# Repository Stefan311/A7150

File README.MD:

# A7150 (CM1910)
### What is the A7150?
It's an old computer from the east german "Robotron" company. See [Wikipedia](https://de.wikipedia.org/wiki/A_7150)
### Why is the rest of this project in german language?
It's made for and with an german audience in mind. The A7150 is rare outside the former east german country anyway.
### Projekte
[IDE-Kontroller AFI-K5173](AFI-K5173/)
[Experimentier-Karte](Exp/)

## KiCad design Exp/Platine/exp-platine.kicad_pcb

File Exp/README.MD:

# Experimentier-Karte für A71x0
## Layout in KiCad
[Revision 1](Platine/)
## Projekte / Beispiele
### JTAG-Flasher
Ein Projekt für den ESP32, das kann benutzt werden, um über WLAN den CPLD zu konfigurieren.
[Flasher](Projekte/esp32_jtag_CPLD_flasher/)
### Einfacher I/O Port
Ein Beispiel für einen einfachen I/O-Port.
[IO-Port](Projekte/simple_io_port/)
### Drucker-Port
Ein zusätzlicher Drucker-Port, kann zum Drucken, oder für Fern-Verbindungen mit dem Norton-Kommander oder Laplink benutzt werden.
[Druckerport](Projekte/printer_port/)
## Tools
### Flasher
Kleine Scripte um Xilinx iMPACT und flashen mit dem ESP32 zu automatisieren.
(Projekte/tools/flash/)
## Beschreibungen / Wissen
...kommt noch...

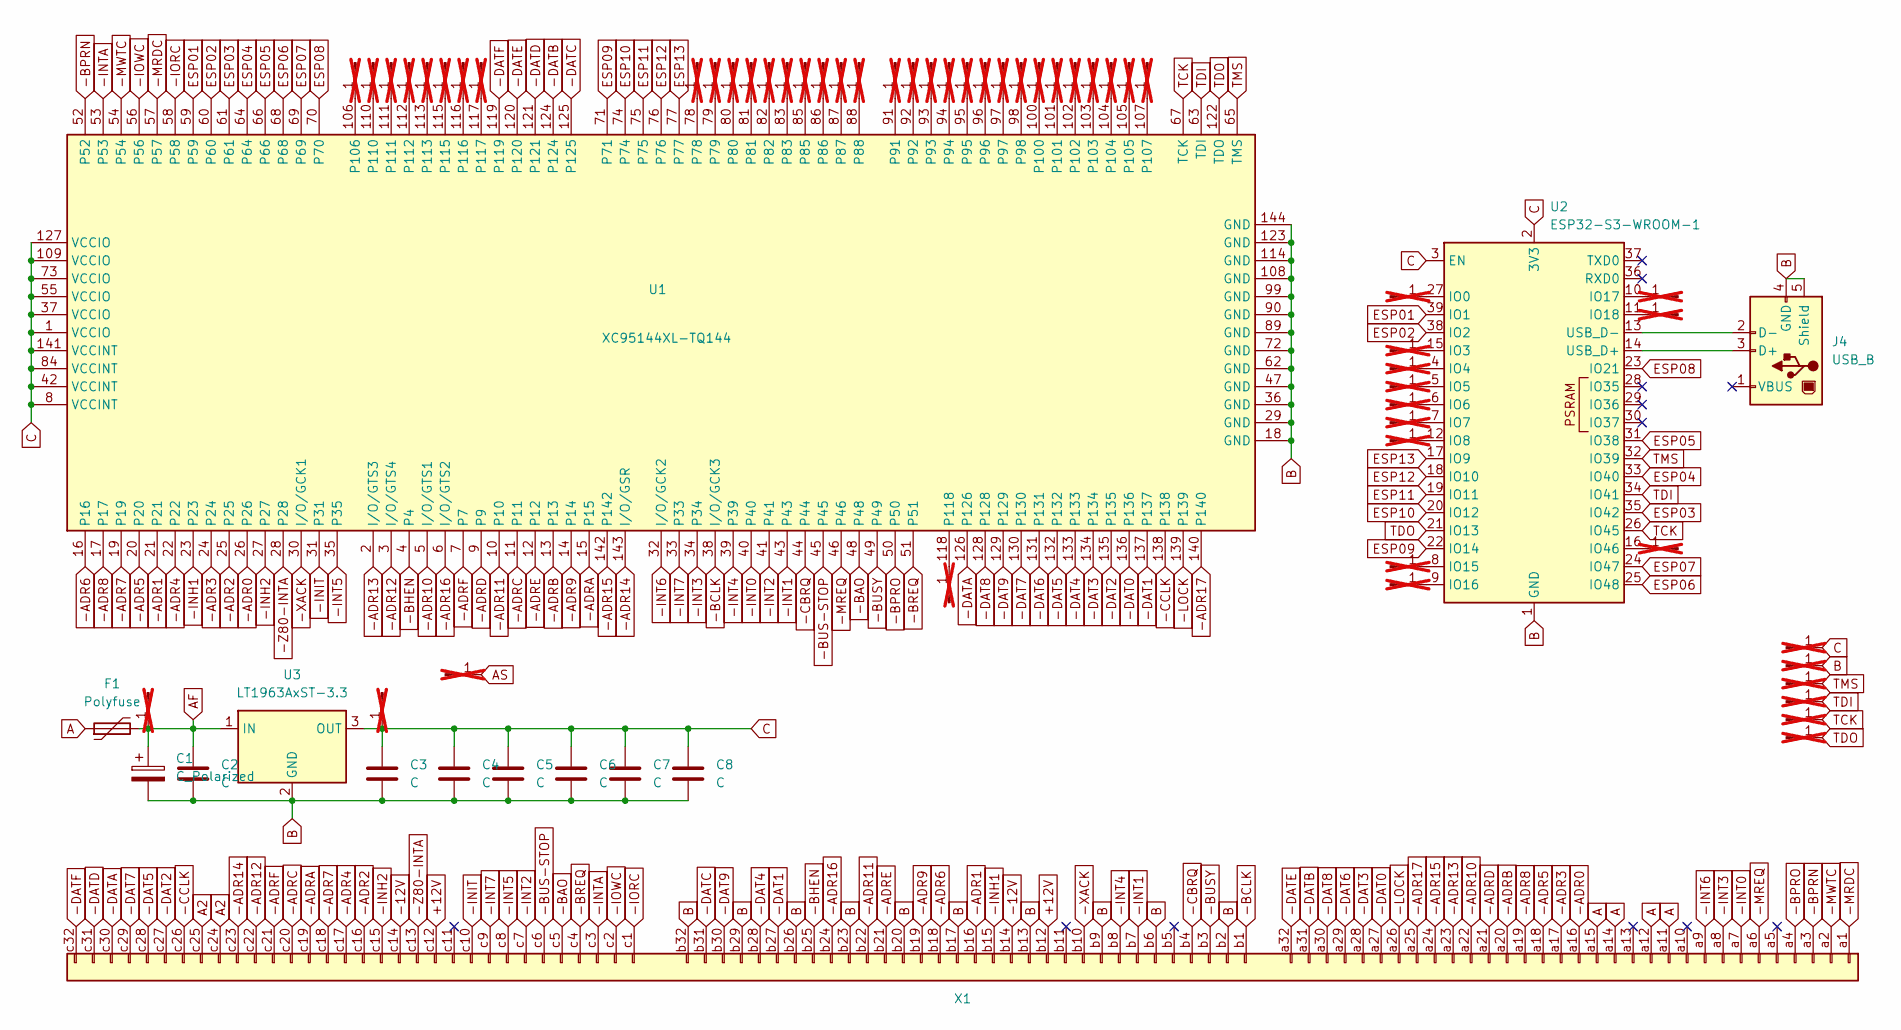
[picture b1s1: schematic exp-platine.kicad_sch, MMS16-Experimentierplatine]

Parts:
C1: C_Polarized; C_Radial_D6.3mm_H5.0mm_P2.50mm
C2, C3, C4, C5, C6, C7, C8: C; C_0805_2012Metric_Pad1.18x1.45mm_HandSolder
F1: Polyfuse; Fuse_Bourns_MF-RG300
J1, J2, J3, J5, J6, J7, J8, J9, J10, J11, J12, J13, J14, J15, J16, J17, J18, J19, J20, J21, J22, J23, J24, J25, J26, J27, J28, J29, J30, J31, J32, J33, J34, J35, J36, J37, J38, J39, J40, J41, J42, J43, J44, J45, J46, J47, J48, J49, J50, J51, J52, J53, J54, J55, J56: Conn_01x01_Pin; PinHeader_1x01_P2.54mm_Vertical; not fitted
J4: USB_B; USB_B_Lumberg_2411_02_Horizontal
U1: XC95144XL-TQ144; TQFP-144_20x20mm_P0.5mm
U2: ESP32-S3-WROOM-1
U3: LT1963AxST-3.3; SOT-223-3_TabPin2
X1: DIN41612_03x32_ABC; DIN41612_C_3x32_Male_Horizontal_THT

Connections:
+12V: X1.b12, X1.c12
-12V: X1.b14, X1.c14
-ADR0: U1.26, X1.a16
-ADR1: U1.21, X1.b16
-ADR2: U1.25, X1.c16
-ADR3: U1.24, X1.a17
-ADR4: U1.22, X1.c17
-ADR5: U1.20, X1.a18
-ADR6: U1.16, X1.b18
-ADR7: U1.19, X1.c18
-ADR8: U1.17, X1.a19
-ADR9: U1.14, X1.b19
-ADR10: U1.5 (I/O/GTS1), X1.a22
-ADR11: U1.10, X1.b22
-ADR12: U1.3 (I/O/GTS4), X1.c22
-ADR13: U1.2 (I/O/GTS3), X1.a23
-ADR14: U1.143 (I/O/GSR), X1.c23
-ADR15: U1.142, X1.a24
-ADR16: U1.6 (I/O/GTS2), X1.b24
-ADR17: U1.140, X1.a25
-ADRA: U1.15, X1.c19
-ADRB: U1.13, X1.a20
-ADRC: U1.11, X1.c20
-ADRD: U1.9, X1.a21
-ADRE: U1.12, X1.b21
-ADRF: U1.7, X1.c21
-BAO: U1.48, X1.c5
-BCLK: U1.38 (I/O/GCK3), X1.b1
-BHEN: U1.4, X1.b25
-BPRN: U1.52, X1.a3
-BPRO: U1.50, X1.a4
-BREQ: U1.51, X1.c4
-BUS-STOP: U1.45, X1.c6
-BUSY: U1.49, X1.b3
-CBRQ: U1.44, X1.b4
-CCLK: U1.138, X1.c26
-DAT0: U1.136, X1.a27
-DAT1: U1.137, X1.b27
-DAT2: U1.135, X1.c27
-DAT3: U1.134, X1.a28
-DAT4: U1.133, X1.b28
-DAT5: U1.132, X1.c28
-DAT6: U1.131, X1.a29
-DAT7: U1.130, X1.c29
-DAT8: U1.128, X1.a30
-DAT9: U1.129, X1.b30
-DATA: U1.126, X1.c30
-DATB: U1.124, X1.a31
-DATC: U1.125, X1.b31
-DATD: U1.121, X1.c31
-DATE: U1.120, X1.a32
-DATF: U1.119, X1.c32
-INH1: U1.23, X1.b15
-INH2: U1.27, X1.c15
-INIT: U1.31, X1.c10
-INT0: U1.40, X1.a7
-INT1: U1.43, X1.b7
-INT2: U1.41, X1.c7
-INT3: U1.34, X1.a8
-INT4: U1.39, X1.b8
-INT5: U1.35, X1.c8
-INT6: U1.32 (I/O/GCK2), X1.a9
-INT7: U1.33, X1.c9
-INTA: U1.53, X1.c3
-IORC: U1.58, X1.c1
-IOWC: U1.56, X1.c2
-LOCK: U1.139, X1.a26
-MRDC: U1.57, X1.a1
-MREQ: U1.46, X1.a6
-MWTC: U1.54, X1.a2
-XACK: U1.30 (I/O/GCK1), X1.b10
-Z80-INTA: U1.28, X1.c13
A: F1.1, X1.a11, X1.a12, X1.a14, X1.a15
A2: X1.c24, X1.c25
AF: C1.1, C2.1, F1.2, J34.1, U3.1 (IN)
AS: J54.1
B: C1.2, C2.2, C3.2, C4.2, C5.2, C6.2, C7.2, C8.2, J4.4 (GND), J4.5 (Shield), J36.1, U1.18 (GND), U1.29 (GND), U1.36 (GND), U1.47 (GND), U1.62 (GND), U1.72 (GND), U1.89 (GND), U1.90 (GND), U1.99 (GND), U1.108 (GND), U1.114 (GND), U1.123 (GND), U1.144 (GND), U2.1 (GND), U2.40 (GND), U2.41 (GND), U3.2 (GND), X1.b2, X1.b6, X1.b9, X1.b13, X1.b17, X1.b20, X1.b23, X1.b26, X1.b29, X1.b32
C: C3.1, C4.1, C5.1, C6.1, C7.1, C8.1, J37.1, J53.1, U1.1 (VCCIO), U1.8 (VCCINT), U1.37 (VCCIO), U1.42 (VCCINT), U1.55 (VCCIO), U1.73 (VCCIO), U1.84 (VCCINT), U1.109 (VCCIO), U1.127 (VCCIO), U1.141 (VCCINT), U2.2 (3V3), U2.3 (EN), U3.3 (OUT)
ESP01: U1.59, U2.39 (IO1)
ESP02: U1.60, U2.38 (IO2)
ESP03: U1.61, U2.35 (IO42)
ESP04: U1.64, U2.33 (IO40)
ESP05: U1.66, U2.31 (IO38)
ESP06: U1.68, U2.25 (IO48)
ESP07: U1.69, U2.24 (IO47)
ESP08: U1.70, U2.23 (IO21)
ESP09: U1.71, U2.22 (IO14)
ESP10: U1.74, U2.20 (IO12)
ESP11: U1.75, U2.19 (IO11)
ESP12: U1.76, U2.18 (IO10)
ESP13: U1.77, U2.17 (IO9)
unnamed: J1.1, U1.118
unnamed: J2.1, U1.117
unnamed: J3.1, U1.116
unnamed: J4.3 (D+), U2.14 (USB_D+)
unnamed: J4.2 (D-), U2.13 (USB_D-)
unnamed: J5.1, U1.115
unnamed: J6.1, U1.113
unnamed: J7.1, U1.112
unnamed: J8.1, U1.111
unnamed: J9.1, U1.110
unnamed: J10.1, U1.107
unnamed: J11.1, U1.106
unnamed: J12.1, U1.105
unnamed: J13.1, U1.103
unnamed: J14.1, U1.104
unnamed: J15.1, U1.98
unnamed: J16.1, U1.100
unnamed: J17.1, U1.101
unnamed: J18.1, U1.102
unnamed: J19.1, U1.80
unnamed: J20.1, U1.91
unnamed: J21.1, U1.92
unnamed: J22.1, U1.93
unnamed: J23.1, U1.94
unnamed: J24.1, U1.95
unnamed: J25.1, U1.96
unnamed: J26.1, U1.97
unnamed: J27.1, U1.81
unnamed: J28.1, U1.82
unnamed: J29.1, U1.83
unnamed: J30.1, U1.85
unnamed: J31.1, U1.86
unnamed: J32.1, U1.87
unnamed: J33.1, U1.88
unnamed: J35.1, U2.4 (IO4)
unnamed: J40.1, U1.78
unnamed: J41.1, U1.79
unnamed: J42.1, U2.5 (IO5)
unnamed: J43.1, U2.6 (IO6)
unnamed: J44.1, U2.7 (IO7)
unnamed: J45.1, U2.8 (IO15)
unnamed: J46.1, U2.9 (IO16)
unnamed: J47.1, U2.10 (IO17)
unnamed: J48.1, U2.11 (IO18)
unnamed: J49.1, U2.12 (IO8)
unnamed: J51.1, U2.15 (IO3)
unnamed: J52.1, U2.16 (IO46)
unnamed: J55.1, U2.27 (IO0)
TCK: J50.1, U1.67 (TCK), U2.26 (IO45)
TDI: J39.1, U1.63 (TDI), U2.34 (IO41)
TDO: J56.1, U1.122 (TDO), U2.21 (IO13)
TMS: J38.1, U1.65 (TMS), U2.32 (IO39)

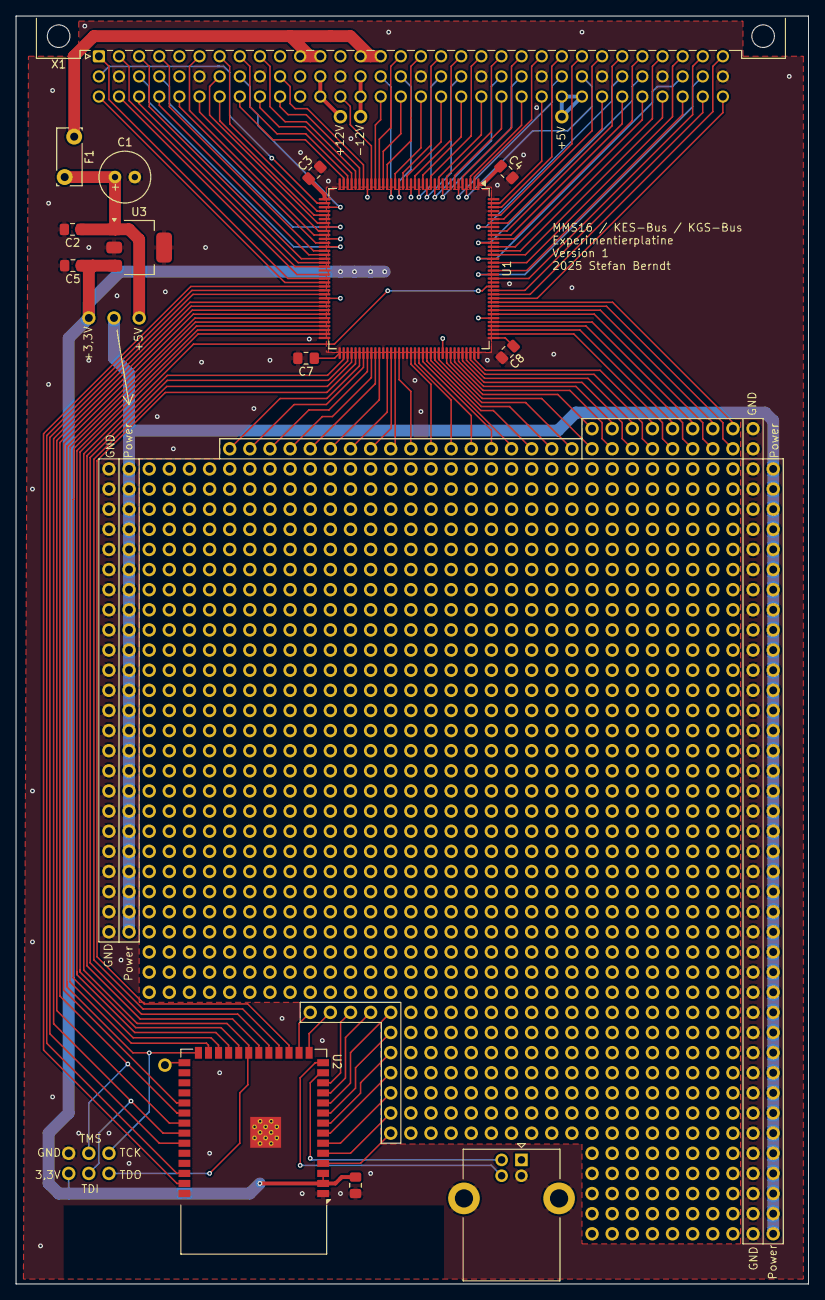
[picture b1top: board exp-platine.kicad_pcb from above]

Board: 2 copper layers, 100.0 x 160.0 mm, 69 parts (0 on the bottom side), 142 nets.

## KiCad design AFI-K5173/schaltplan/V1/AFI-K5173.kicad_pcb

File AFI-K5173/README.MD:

# AFI-K5173 - IDE Controller für A7150 (CM1910)
AFI ist einen Platine, mit dem IDE-Festplatten an das Datenträger-Subsystem des A7150 angeschlossen werden können.
### Welche Features unterstützt AFI-K5173?
* 1 IDE Kanal für 2 Geräte
* DMA-Fähig
* Boot-Fähig
* Firmware Flashrom im System beschreibbar
* Iomega ZIP100 Atapi Laufwerke als Festplatte nutzbar
* Unterstützung Arduino-USB-Board auf Basis vom CH375B zur Verwendung von USB-Sticks (Achtung: Platine muss auf 5V Signalpegel umbebaut werden!)

### Welche Features sind in Vorbereitung?

* Firmware mit DMA-Übertragung direkt in den Host-Speicher für höhere Übertragungsrate
* Firmware "All in One"

### Teile des Projekts:

[Schaltung und PCB Layout in KiCad und PDF](schaltplan/)

[Materialliste](schaltplan/V1/Materialliste.txt)

[Firmware](firmware/)

[Tools](tools/)

[Treiber](treiber/)

[Anleitungen: Hardware-Test](knowhow/Hardwaretest.MD)

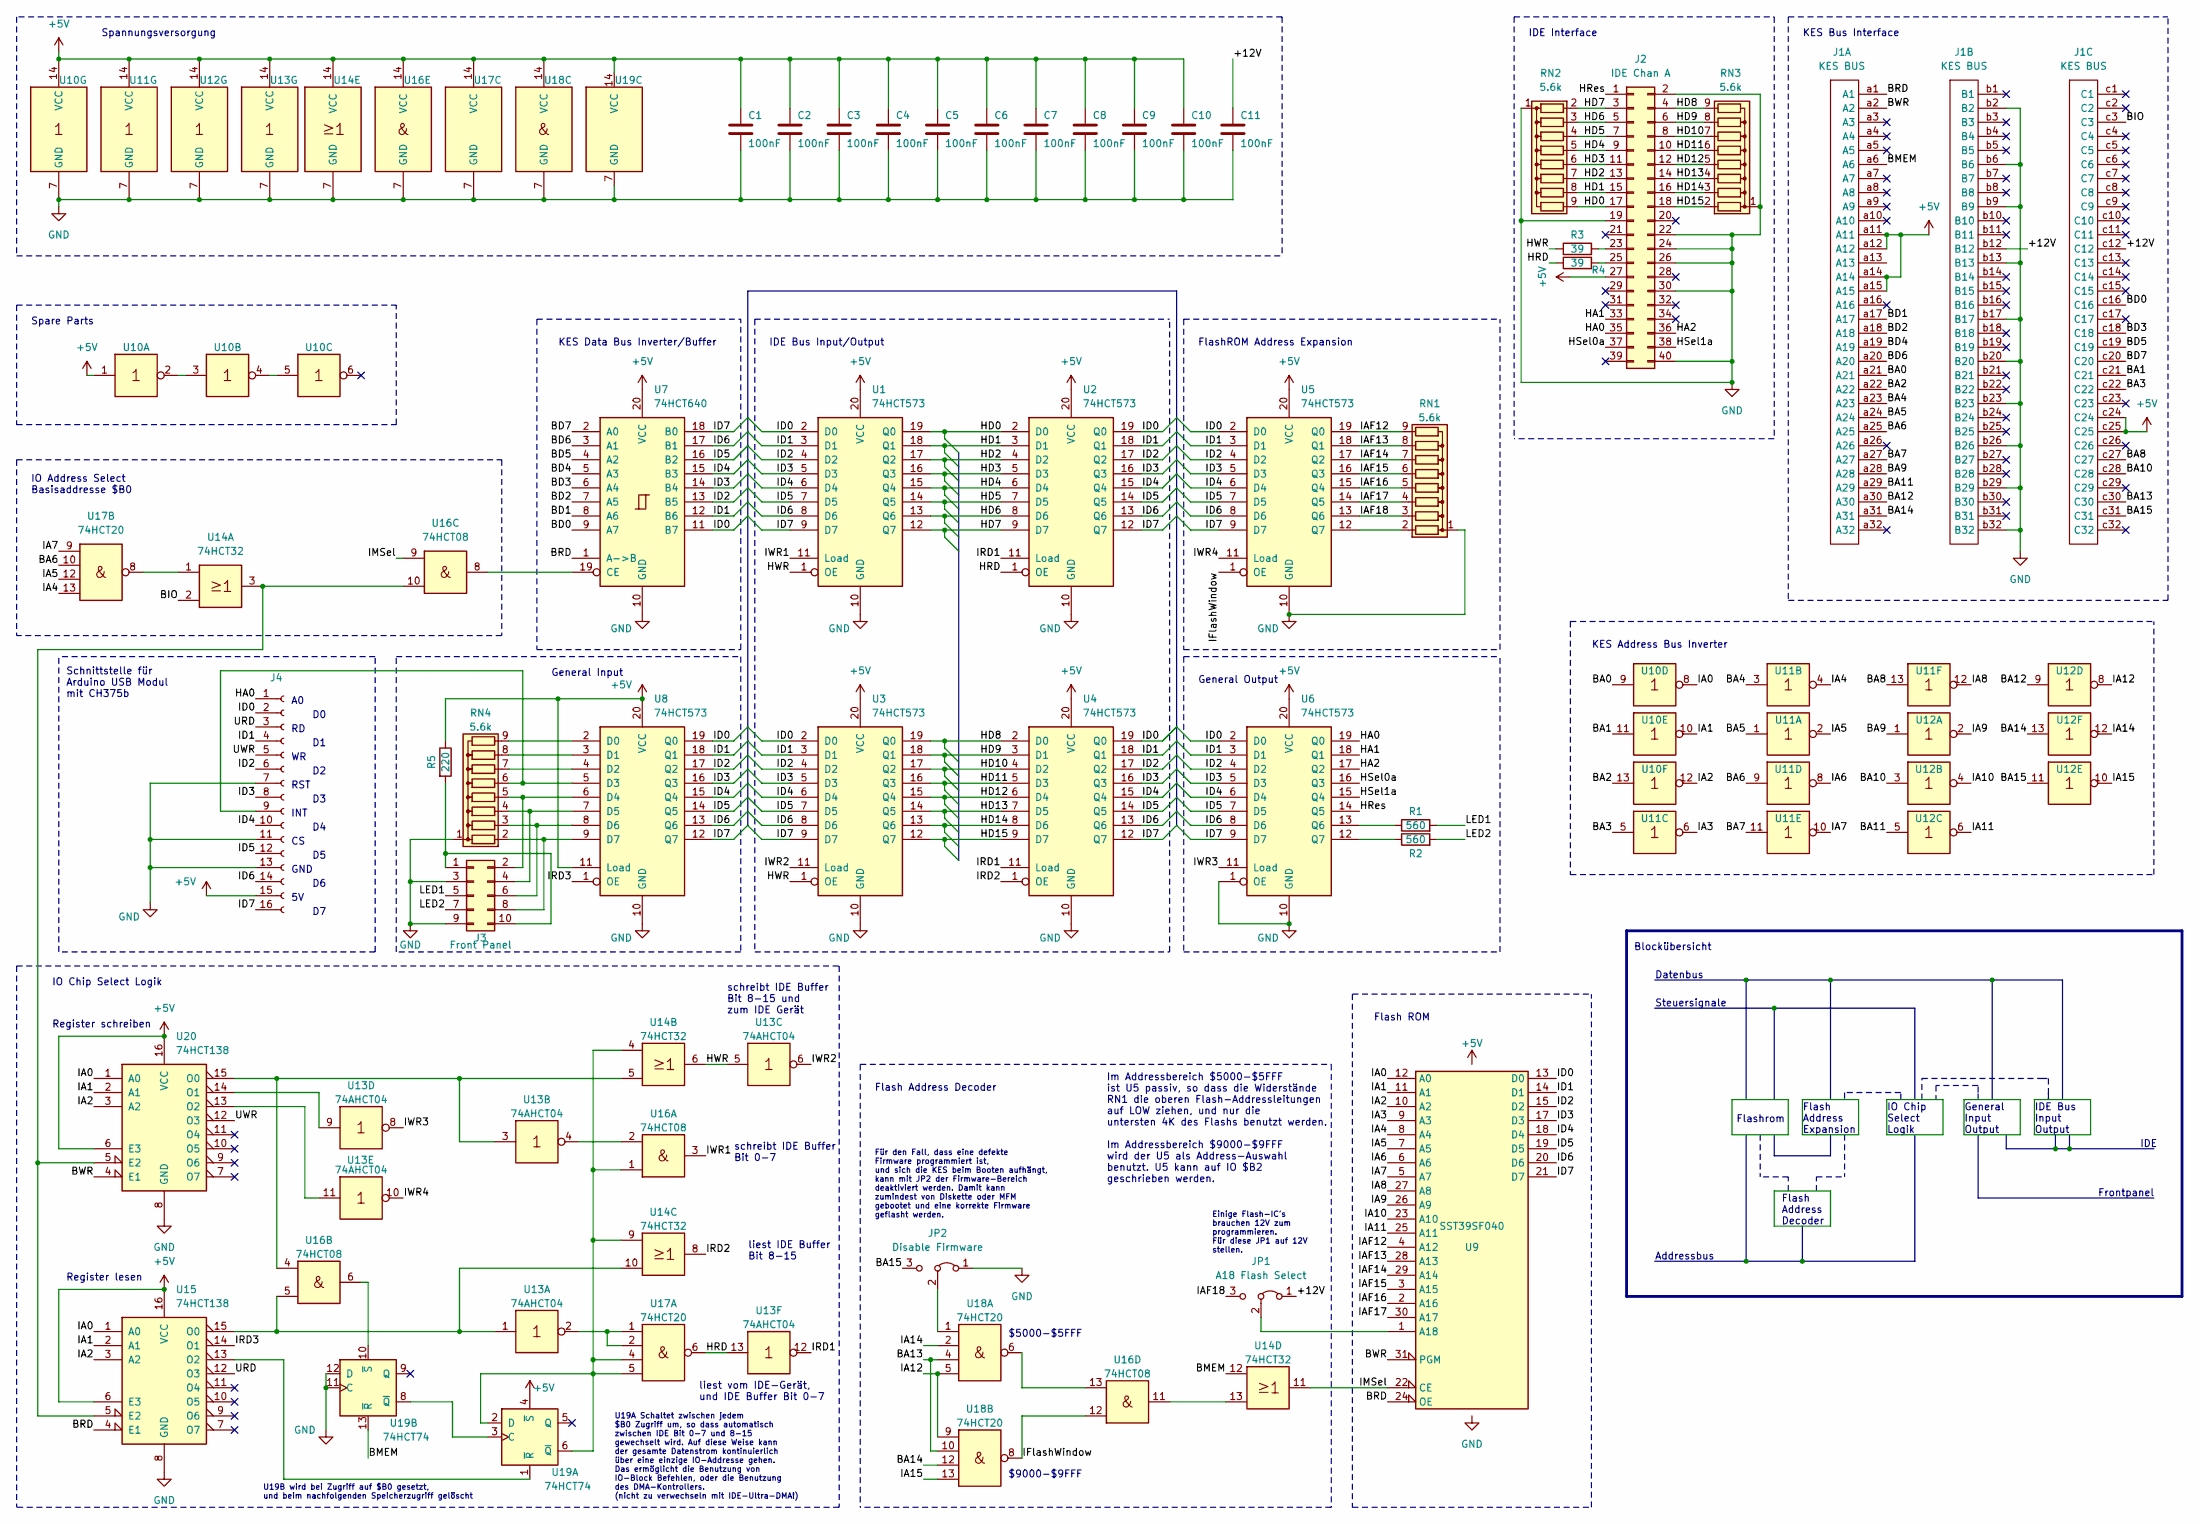
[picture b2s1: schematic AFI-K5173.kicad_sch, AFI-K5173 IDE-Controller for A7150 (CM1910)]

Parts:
C1, C2, C3, C4, C5, C6, C7, C8, C9, C10, C11: 100nF; C_Rect_L7.0mm_W2.0mm_P5.00mm
J1: KES BUS; DIN41612_C_3x32_Male_Horizontal_THT
J2: IDE Chan A; PinHeader_2x20_P2.54mm_Horizontal
J3: Front Panel; PinHeader_2x05_P2.54mm_Horizontal
J4: Conn_01x16_Female; PinSocket_2x08_P2.54mm_Vertical
JP1: A18 Flash Select; PinHeader_1x03_P2.54mm_Vertical
JP2: Disable Firmware; PinHeader_1x03_P2.54mm_Vertical
R1, R2: 560; R_Axial_DIN0309_L9.0mm_D3.2mm_P2.54mm_Vertical
R3, R4: 39; R_Axial_DIN0309_L9.0mm_D3.2mm_P2.54mm_Vertical
R5: 220; R_Axial_DIN0309_L9.0mm_D3.2mm_P2.54mm_Vertical
RN1, RN2, RN3, RN4: 5.6k; R_Array_SIP9
U1, U2, U3, U4, U5, U6, U8: 74HCT573; DIP-20_W7.62mm
U7: 74HCT640; DIP-20_W7.62mm
U9: SST39SF040; DIP-32_W15.24mm
U10, U11, U12: 74HCT04; DIP-14_W7.62mm
U13: 74AHCT04; DIP-14_W7.62mm
U14: 74HCT32; DIP-14_W7.62mm
U15, U20: 74HCT138; DIP-16_W7.62mm
U16: 74HCT08; DIP-14_W7.62mm
U17, U18: 74HCT20; DIP-14_W7.62mm
U19: 74HCT74; DIP-14_W7.62mm

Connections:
+5V: C1.1, C2.1, C3.1, C4.1, C5.1, C6.1, C7.1, C8.1, C9.1, C10.1, J1.a11 (A11), J1.a12 (A12), J1.a14 (A14), J1.a15 (A15), J1.c24 (C24), J1.c25 (C25), J2.27, J4.15, R5.1, U1.20 (VCC), U2.20 (VCC), U3.20 (VCC), U4.20 (VCC), U5.20 (VCC), U6.20 (VCC), U7.20 (VCC), U8.11 (Load), U8.20 (VCC), U9.32 (VCC), U10.1, U10.14 (VCC), U11.14 (VCC), U12.14 (VCC), U13.14 (VCC), U14.14 (VCC), U15.6 (E3), U15.16 (VCC), U16.14 (VCC), U17.14 (VCC), U18.14 (VCC), U19.4 (~S), U19.14 (VCC), U20.6 (E3), U20.16 (VCC)
/+12V: C11.1, J1.b12 (B12), J1.c12 (C12), JP1.1 (A)
/BA0: J1.a21 (A21), U10.9
/BA1: J1.c21 (C21), U10.11
/BA2: J1.a22 (A22), U10.13
/BA3: J1.c22 (C22), U11.5
/BA4: J1.a23 (A23), U11.3
/BA5: J1.a24 (A24), U11.1
/BA6: J1.a25 (A25), U11.9, U17.10
/BA7: J1.a27 (A27), U11.11
/BA8: J1.c27 (C27), U11.13
/BA9: J1.a28 (A28), U12.1
/BA10: J1.c28 (C28), U12.3
/BA11: J1.a29 (A29), U12.5
/BA12: J1.a30 (A30), U12.9
/BA13: J1.c30 (C30), U18.4, U18.10
/BA14: J1.a31 (A31), U12.13, U18.12
/BA15: J1.c31 (C31), JP2.3 (B), U12.11
/BD0: J1.c16 (C16), U7.9 (A7)
/BD1: J1.a17 (A17), U7.8 (A6)
/BD2: J1.a18 (A18), U7.7 (A5)
/BD3: J1.c18 (C18), U7.6 (A4)
/BD4: J1.a19 (A19), U7.5 (A3)
/BD5: J1.c19 (C19), U7.4 (A2)
/BD6: J1.a20 (A20), U7.3 (A1)
/BD7: J1.c20 (C20), U7.2 (A0)
/BIO: J1.c3 (C3), U14.2
/BMEM: J1.a6 (A6), U14.12, U19.13 (~R)
/BRD: J1.a1 (A1), U7.1 (A->B), U9.24 (OE), U15.4 (E1)
/BWR: J1.a2 (A2), U9.31 (PGM), U20.4 (E1)
/HA0: J2.35, J4.1, U6.19 (Q0)
/HA1: J2.33, U6.18 (Q1)
/HA2: J2.36, U6.17 (Q2)
/HD0: J2.17, RN2.9 (R8), U1.19 (Q0), U2.2 (D0)
/HD1: J2.15, RN2.8 (R7), U1.18 (Q1), U2.3 (D1)
/HD2: J2.13, RN2.7 (R6), U1.17 (Q2), U2.4 (D2)
/HD3: J2.11, RN2.6 (R5), U1.16 (Q3), U2.5 (D3)
/HD4: J2.9, RN2.5 (R4), U1.15 (Q4), U2.6 (D4)
/HD5: J2.7, RN2.4 (R3), U1.14 (Q5), U2.7 (D5)
/HD6: J2.5, RN2.3 (R2), U1.13 (Q6), U2.8 (D6)
/HD7: J2.3, RN2.2 (R1), U1.12 (Q7), U2.9 (D7)
/HD8: J2.4, RN3.9 (R8), U3.19 (Q0), U4.2 (D0)
/HD9: J2.6, RN3.8 (R7), U3.18 (Q1), U4.3 (D1)
/HD10: J2.8, RN3.7 (R6), U3.17 (Q2), U4.4 (D2)
/HD11: J2.10, RN3.6 (R5), U3.16 (Q3), U4.5 (D3)
/HD12: J2.12, RN3.5 (R4), U3.15 (Q4), U4.6 (D4)
/HD13: J2.14, RN3.4 (R3), U3.14 (Q5), U4.7 (D5)
/HD14: J2.16, RN3.3 (R2), U3.13 (Q6), U4.8 (D6)
/HD15: J2.18, RN3.2 (R1), U3.12 (Q7), U4.9 (D7)
/HRD: R4.1, U2.1 (OE), U13.13, U17.6
/HRes: J2.1, U6.14 (Q5)
/HSel0a: J2.37, U6.16 (Q3)
/HSel1a: J2.38, U6.15 (Q4)
/HWR: R3.1, U1.1 (OE), U3.1 (OE), U13.5, U14.6
/IA0: U9.12 (A0), U10.8, U15.1 (A0), U20.1 (A0)
/IA1: U9.11 (A1), U10.10, U15.2 (A1), U20.2 (A1)
/IA2: U9.10 (A2), U10.12, U15.3 (A2), U20.3 (A2)
/IA3: U9.9 (A3), U11.6
/IA4: U9.8 (A4), U11.4, U17.13
/IA5: U9.7 (A5), U11.2, U17.12
/IA6: U9.6 (A6), U11.8
/IA7: U9.5 (A7), U11.10, U17.9
/IA8: U9.27 (A8), U11.12
/IA9: U9.26 (A9), U12.2
/IA10: U9.23 (A10), U12.4
/IA11: U9.25 (A11), U12.6
/IA12: U12.8, U18.5, U18.9
/IA14: U12.12, U18.2
/IA15: U12.10, U18.13
/IAF12: RN1.9 (R8), U5.19 (Q0), U9.4 (A12)
/IAF13: RN1.8 (R7), U5.18 (Q1), U9.28 (A13)
/IAF14: RN1.7 (R6), U5.17 (Q2), U9.29 (A14)
/IAF15: RN1.6 (R5), U5.16 (Q3), U9.3 (A15)
/IAF16: RN1.5 (R4), U5.15 (Q4), U9.2 (A16)
/IAF17: RN1.4 (R3), U5.14 (Q5), U9.30 (A17)
/IAF18: JP1.3 (B), RN1.3 (R2), U5.13 (Q6)
/ID0: J4.2, U1.2 (D0), U2.19 (Q0), U3.2 (D0), U4.19 (Q0), U5.2 (D0), U6.2 (D0), U7.11 (B7), U8.19 (Q0), U9.13 (D0)
/ID1: J4.4, U1.3 (D1), U2.18 (Q1), U3.3 (D1), U4.18 (Q1), U5.3 (D1), U6.3 (D1), U7.12 (B6), U8.18 (Q1), U9.14 (D1)
/ID2: J4.6, U1.4 (D2), U2.17 (Q2), U3.4 (D2), U4.17 (Q2), U5.4 (D2), U6.4 (D2), U7.13 (B5), U8.17 (Q2), U9.15 (D2)
/ID3: J4.8, U1.5 (D3), U2.16 (Q3), U3.5 (D3), U4.16 (Q3), U5.5 (D3), U6.5 (D3), U7.14 (B4), U8.16 (Q3), U9.17 (D3)
/ID4: J4.10, U1.6 (D4), U2.15 (Q4), U3.6 (D4), U4.15 (Q4), U5.6 (D4), U6.6 (D4), U7.15 (B3), U8.15 (Q4), U9.18 (D4)
/ID5: J4.12, U1.7 (D5), U2.14 (Q5), U3.7 (D5), U4.14 (Q5), U5.7 (D5), U6.7 (D5), U7.16 (B2), U8.14 (Q5), U9.19 (D5)
/ID6: J4.14, U1.8 (D6), U2.13 (Q6), U3.8 (D6), U4.13 (Q6), U5.8 (D6), U6.8 (D6), U7.17 (B1), U8.13 (Q6), U9.20 (D6)
/ID7: J4.16, U1.9 (D7), U2.12 (Q7), U3.9 (D7), U4.12 (Q7), U5.9 (D7), U6.9 (D7), U7.18 (B0), U8.12 (Q7), U9.21 (D7)
/IFlashWindow: U5.1 (OE), U16.12, U18.8
/IMSel: U9.22 (CE), U14.11, U16.9
/IRD1: U2.11 (Load), U4.11 (Load), U13.12
/IRD2: U4.1 (OE), U14.8
/IRD3: U8.1 (OE), U15.14 (O1)
/IWR1: U1.11 (Load), U16.3
/IWR2: U3.11 (Load), U13.6
/IWR3: U6.11 (Load), U13.8
/IWR4: U5.11 (Load), U13.10
/LED1: J3.5, R1.2
/LED2: J3.7, R2.2
/URD: J4.3, U15.12 (O3)
/UWR: J4.5, U20.12 (O3)
GND: C1.2, C2.2, C3.2, C4.2, C5.2, C6.2, C7.2, C8.2, C9.2, C10.2, C11.2, J1.b2 (B2), J1.b6 (B6), J1.b9 (B9), J1.b13 (B13), J1.b17 (B17), J1.b20 (B20), J1.b23 (B23), J1.b26 (B26), J1.b29 (B29), J1.b32 (B32), J2.2, J2.19, J2.22, J2.24, J2.26, J2.30, J2.40, J3.3, J3.9, J4.7, J4.11, J4.13, JP2.1 (A), RN1.1 (common), RN2.1 (common), RN3.1 (common), RN4.1 (common), U1.10 (GND), U2.10 (GND), U3.10 (GND), U4.10 (GND), U5.10 (GND), U6.1 (OE), U6.10 (GND), U7.10 (GND), U8.10 (GND), U9.16 (GND), U10.7 (GND), U11.7 (GND), U12.7 (GND), U13.7 (GND), U14.7 (GND), U15.8 (GND), U16.7 (GND), U17.7 (GND), U18.7 (GND), U19.7 (GND), U19.11 (C), U19.12 (D), U20.8 (GND)
unnamed: J2.23, R3.2
unnamed: J2.25, R4.2
unnamed: J3.1, J3.10, R5.2
unnamed: J3.2, RN4.5 (R4), U8.6 (D4)
unnamed: J3.4, RN4.4 (R3), U8.7 (D5)
unnamed: J3.6, RN4.3 (R2), U8.8 (D6)
unnamed: J3.8, RN4.2 (R1), U8.9 (D7)
unnamed: J4.9, RN4.6 (R5), U8.5 (D3)
unnamed: JP1.2 (C), U9.1 (A18)
unnamed: JP2.2 (C), U18.1
unnamed: RN1.2 (R1), U5.12 (Q7)
unnamed: RN4.7 (R6), U8.4 (D2)
unnamed: RN4.8 (R7), U8.3 (D1)
unnamed: RN4.9 (R8), U8.2 (D0)
unnamed: R1.1, U6.13 (Q6)
unnamed: R2.1, U6.12 (Q7)
unnamed: U7.19 (CE), U16.8
unnamed: U10.2, U10.3
unnamed: U10.4, U10.5
unnamed: U13.2, U17.1, U17.2
unnamed: U13.4, U16.2
unnamed: U14.1, U17.8
unnamed: U14.13, U16.11
unnamed: U14.3, U15.5 (E2), U16.10, U20.5 (E2)
unnamed: U13.1, U14.10, U15.15 (O0), U16.5
unnamed: U15.13 (O2), U19.1 (~R)
unnamed: U16.13, U18.6
unnamed: U19.3 (C), U19.8 (~Q)
unnamed: U14.4, U14.9, U16.1, U17.4, U17.5, U19.2 (D), U19.6 (~Q)
unnamed: U16.6, U19.10 (~S)
unnamed: U13.3, U14.5, U16.4, U20.15 (O0)
unnamed: U13.9, U20.14 (O1)
unnamed: U13.11, U20.13 (O2)

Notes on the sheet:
General Output
liest IDE Buffer Bit 8-15
KES Address Bus Inverter
GND
KES Bus Interface
FlashROM Address Expansion
Flash Address Decoder
IO Address Select Basisaddresse $B0
Frontpanel
KES Data Bus Inverter/Buffer
Flash ROM
$9000-$9FFF
Flash Address Expansion
IDE Bus Input Output
liest vom IDE-Gerät, und IDE Buffer Bit 0-7
U19B wird bei Zugriff auf $B0 gesetzt, und beim nachfolgenden Speicherzugriff gelöscht
Im Addressbereich $5000-$5FFF ist U5 passiv, so dass die Widerstände RN1 die oberen Flash-Addressleitungen auf LOW ziehen, und nur die untersten 4K des Flashs benutzt werden. Im Addressbereich $9000-$9FFF wird der U5 als Address-Auswahl benutzt. U5 kann auf IO $B2 geschrieben werden.
schreibt IDE Buffer Bit 0-7
Addressbus
General Input Output
Register schreiben
RST
U19A Schaltet zwischen jedem $B0 Zugriff um, so dass automatisch zwischen IDE Bit 0-7 und 8-15 gewechselt wird. Auf diese Weise kann der gesamte Datenstrom kontinuierlich über eine einzige IO-Addresse gehen. Das ermöglicht die Benutzung von IO-Block Befehlen, oder die Benutzung des DMA-Kontrollers.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
INT
Flashrom
schreibt IDE Buffer Bit 8-15 und zum IDE Gerät
IO Chip Select Logik
Datenbus
Flash Address Decoder
Einige Flash-IC's brauchen 12V zum programmieren. Für diese JP1 auf 12V stellen.
IDE
Steuersignale
Blockübersicht
Schnittstelle für Arduino USB Modul mit CH375b
IDE Interface
IDE Bus Input/Output
IO Chip Select Logik
Für den Fall, dass eine defekte Firmware programmiert ist, und sich die KES beim Booten aufhängt, kann mit JP2 der Firmware-Bereich deaktiviert werden. Damit kann zumindest von Diskette oder MFM gebootet und eine korrekte Firmware geflasht werden.
General Input
Spare Parts

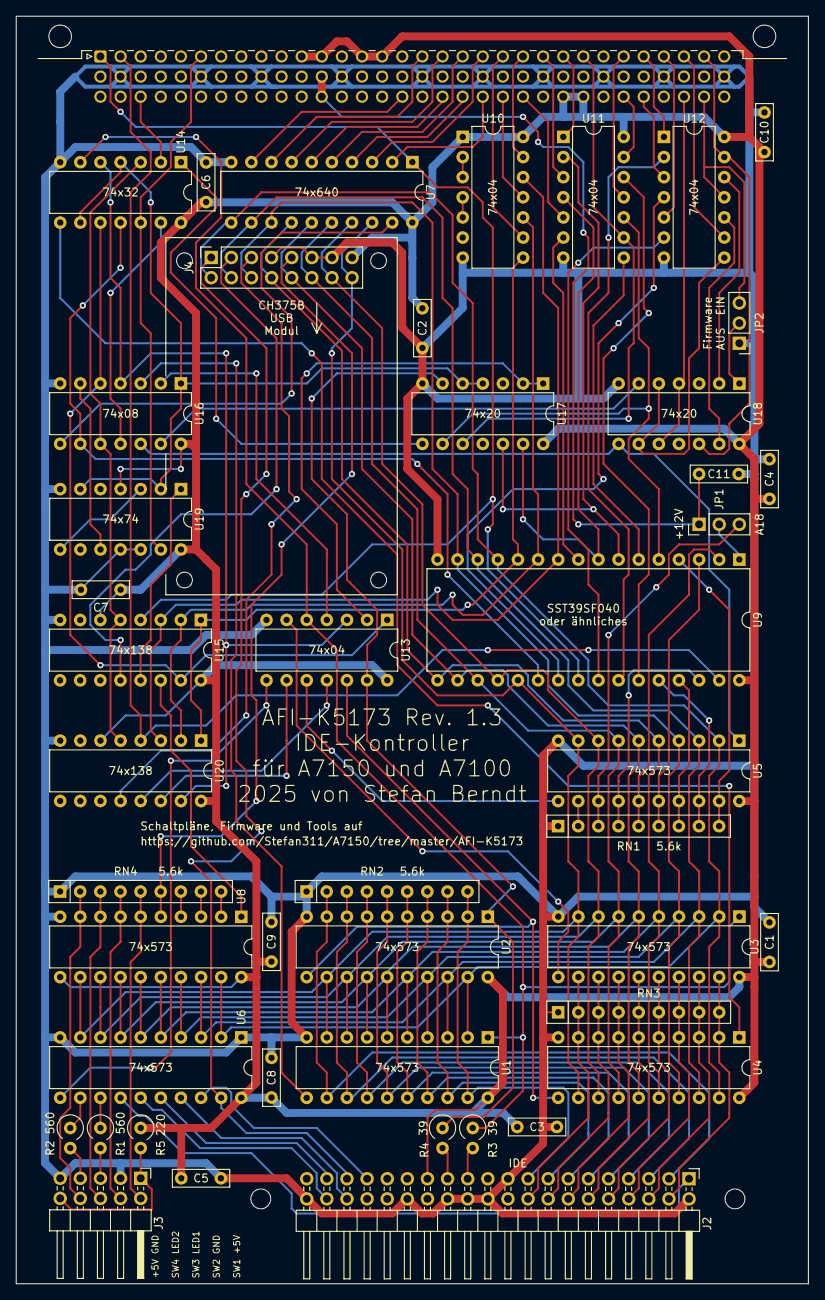
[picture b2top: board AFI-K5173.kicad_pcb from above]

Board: 2 copper layers, 100.0 x 160.0 mm, 46 parts (0 on the bottom side), 131 nets.

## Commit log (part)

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2022-08-30 A7150: Initial commit
2022-09-04 Neues Tool: CRCTOOL
2022-09-11 Bigfixes AFITEST
2022-09-12 AFIFLASH Optimierungen auf Geschwindigkeit
2022-09-15 Firmware-Version: ROM-Disk
2022-09-25 Firmware-Version: IDE V0.1
2022-09-28 Firmware-Version: IDE V0.2 - Bugfix CHS-LBA Umrechnung - IDE Statusabfrage vor Lesen/Schreiben und nach Schreiben - einfacher Error-Log - verlaengerte Wartezeit beim Initialisieren
2022-09-30 Beschreibung: Test der Platine
2022-09-30 Formatierung
2022-09-30 Grrrr. MARKDOWN.
2022-10-03 Firmware-Version: IDE V0.3
2022-10-04 Bigfix Schaltung/PCB: Pin 39 des IDE-Steckers darf nicht auf Masse liegen. Das verursacht eine exrem lange Bootphase bei bestimmten Platten-Konfigurationen.
2022-10-09 Neues Tool: Fixwinch
2022-10-14 Firmware-Version: IDE V0.4
2022-10-18 Firmware-Version: IDE CHS-Modus V0.1
2022-10-21 Create LICENSE
2022-10-30 Neues Tool: CLONEHDD
2022-11-16 Firmware-Version: IDE CHS-Modus V0.2
2023-01-20 Firmware-Version: ATAPI V0.1
2023-04-05 Schaltung/PCB: Anschluss für USB-Kontroller-Platine hinzugefügt
2023-04-15 Materialliste, USB-Unterstützung für das Testprogramm, paar optische Kleinigkeiten
2023-04-15 Update Materialliste.txt
    Fix TAB
2023-04-30 * Unterstützung für CH375 USB-Chip in Firmware (IDE_CHS) und DOS-Gerätetreiber (AFICH375) * Bugfix AFITest: Wiederherstellung des B-Kanals nach Programmende
2023-05-14 AFIFLASH: Alle Zeitkritischen Programmteile in die KES verlagert. Dadurch sollten alle unterstützen Flash-IC's geflasht werden können.
2023-05-14 Markdown... Meine ganz spezielle Liebe...
2023-07-23 Firmware-Version: IDE_CHS V0.4 + massiver Gewinn an Übertragungsgeschwindigkeit durch DMA-Transfer direkt ins Host-System (ca. 380kb/s)
2023-09-23 Firmware-Version: IDE_CHS V0.5 - Unterstuetzung fuer LBA Addressmodus aus IDE(LBA) V0.4 importiert - Automatische Auswahl, ob CHS oder LBA verwendet wird - Das LED-Leuchten ist etwas verlaengert, dam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
2025-02-16 Firmware-Version: ATAPI V0.2 und IDE_CHA V0.6 ATAPI: - Unterstützung für USB - Bugfix Fehler beim Boot IDE_CHS: - Wartezeit beim Systemstart verkürzt (nur bemerkbar wenn keine IDE-Platte angschlossen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
2025-02-16 Schaltungsänderung und Layout V0.3
2025-02-26 AFIFLASH: - Bugfix: Absturz bei bestimmten AFS-Versionen - Abfrage bei zu kleiner BIN-Datei entfernt. Die ist sinnlos, da immer zutreffend.
2025-03-06 Clonehdd kann bei Lesefehlern nun das Lesen wiederholen. Wie oft ist einstellbar.
2025-12-08 Experimantierplatine
2025-12-15 SPI-Register
2025-12-31 WLAN-Konfimenü für die Grundvariante des CPLD-Flashers
2025-12-31 WLAN-Konfi-Menü für den SPI-Registertest
2026-05-20 Experimentierplatine: Busmaster-Funktion
